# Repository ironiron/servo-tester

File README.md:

Small servo tester designed for Attiny13a. Pulse width 0.5-2.5ms; 3 modes: oscillating, normal and neutrum.

Author: Rafał Mazurkiewicz
contact: raf.mazurkiewicz@op.pl

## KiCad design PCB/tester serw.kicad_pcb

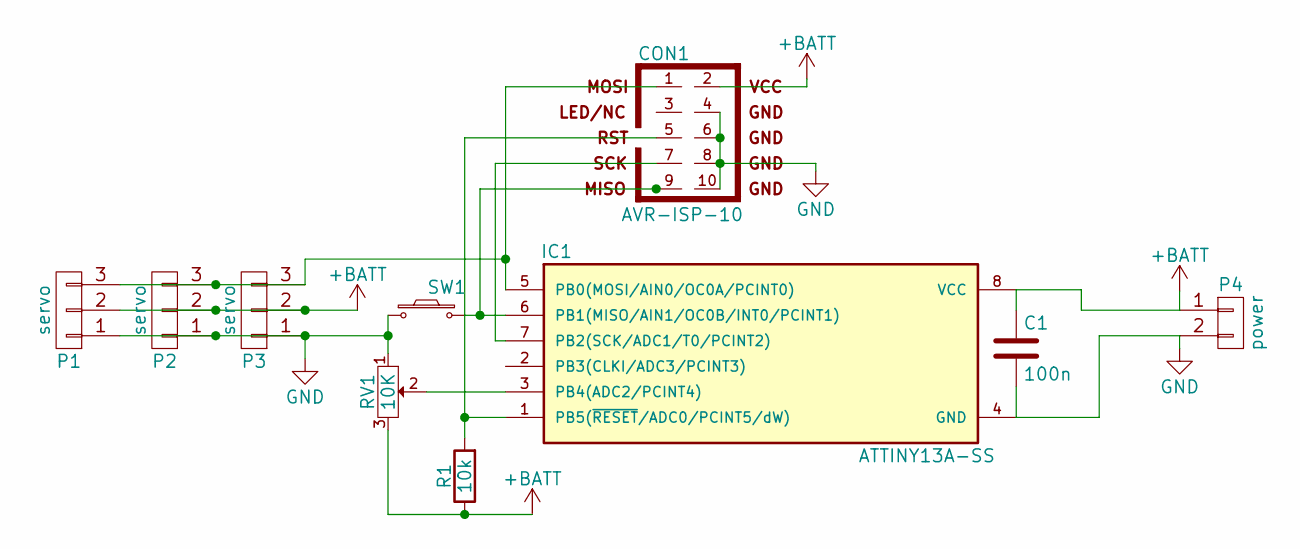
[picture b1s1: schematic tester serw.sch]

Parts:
C1: 100n; C_0805_HandSoldering
CON1: AVR-ISP-10; IDC_Header_Straight_10pins
IC1: ATTINY13A-SS; SOIJ-8_5.3x5.3mm_Pitch1.27mm
P1, P2, P3: servo; Pin_Header_Straight_1x03_Pitch2.54mm
P4: power; Pin_Header_Straight_1x02_Pitch2.54mm
R1: 10k; R_0805_HandSoldering
RV1: 10K; Potentiometer_Alps-RK16-single
SW1: button; SW_SPST_REED_CT05-XXXX-G1

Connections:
+BATT: C1.1, CON1.2, IC1.8 (VCC), P1.2, P2.2, P3.2, P4.1, R1.1, RV1.3
GND: C1.2, CON1.4, CON1.6, CON1.8, CON1.10, IC1.4 (GND), P1.1, P2.1, P3.1, P4.2, RV1.1, SW1.1
unnamed: CON1.1, IC1.5 (PB0(MOSI/AIN0/OC0A/PCINT0)), P1.3, P2.3, P3.3
unnamed: CON1.5, IC1.1 (PB5(~RESET~/ADC0/PCINT5/dW)), R1.2
unnamed: CON1.7, IC1.7 (PB2(SCK/ADC1/T0/PCINT2))
unnamed: CON1.9, IC1.6 (PB1(MISO/AIN1/OC0B/INT0/PCINT1)), SW1.2
unnamed: IC1.3 (PB4(ADC2/PCINT4)), RV1.2

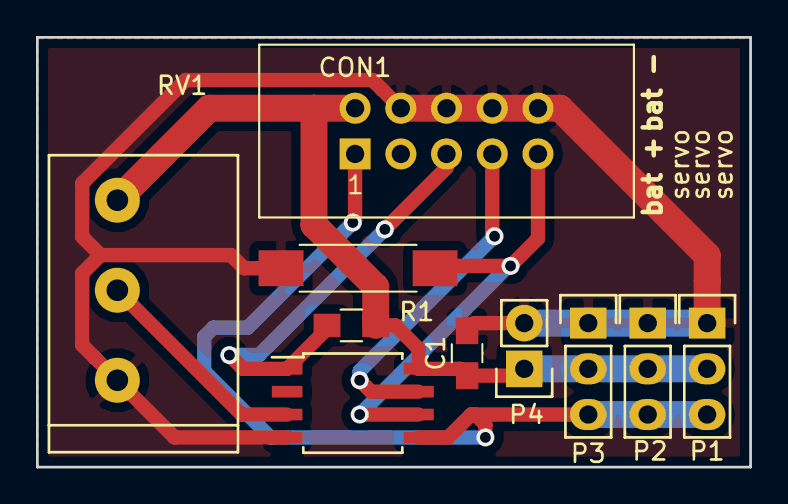
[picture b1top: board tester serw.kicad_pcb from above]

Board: 2 copper layers, 39.6 x 23.9 mm, 10 parts (0 on the bottom side), 7 nets.

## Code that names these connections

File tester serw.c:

/*
 * tester_serw.c
 *
 * Created: 2015-01-10 17:53:29
 *  Author: Rafał Mazurkiewicz
 Servo tester. In period of 20ms sends 0,5-2,5ms impulse to servo.
 potentiometer PB4
 button PB1 INT0 long press (>1s) servo is oscillating, short press- neutrum.
 Return to normal mode by pressing button (if was oscillating), or by moving potentiometer.
 output PB0
 
 tester serw wysyła co ok. 20ms impuls o długości 0,5-2,5ms do serwa.
 Potencjometr na PB4
 Przycisk na PB1 INT0. długie (>1s) naciśnięcie serwo oscyluje, krótkie stoi w neutrum 
 powrót do pracy swobodnej potencjometrem, bądź przyciskiem jeśli wcześniej był w tryb oscylacji.
 wyjście PB0
 */ 

#include <avr/io.h>
#include <util/delay.h>
#include <avr/interrupt.h>

#define button (1<<PB1)
#define output (1<<PB0)
#define potenciometer (1<<PB4)
#define set_output PORTB|=(1<<PB0)
#define clear_output PORTB&=~(1<<PB0)
#define TCNT0_BASE 105 // tick resolution for manipulating PWM lenght is 150, thus 255-150=105.

//SPI related
#define SET_SS //PORTB|=(1<<PB5)
#define SET_CLOCK PORTB|=(1<<PB2)
#define SET_MOSI PORTB|=(1<<PB3)

#define RESET_SS //PORTB&=~(1<<PB5)
#define RESET_CLOCK PORTB&=~(1<<PB2)
#define RESET_MOSI PORTB&=~(1<<PB3)


volatile uint8_t adc=0;
volatile uint8_t remember=0;
volatile uint16_t ticks=0;
volatile uint8_t position=0;
volatile uint8_t overflows_left=0;

enum current_mode {normal, neutral, oscillating} current_mode;
enum direction {left, right} direction;
enum state {waiting, PWM, PWM_overflows} state;
	
void _send_SPI(uint8_t data)
{
	//CPOL=0
	//CPHA=0
	RESET_CLOCK;
	RESET_MOSI;
	RESET_SS;
	for(uint8_t i=0;i<8;i++)
	{
		if((data<<i) & 0x80)
		{
			SET_MOSI;
		}
		else
		{
			RESET_MOSI;
		}
		_delay_us(10);
		SET_CLOCK;
		_delay_us(10);
		RESET_CLOCK;
	}
	SET_SS;
}

void calculate_ticks(void)
{
	switch (current_mode)
	{
		case normal:
		ticks=adc*3/2+75;// 1 adc=10ms; add 75 so begins counting fom 0,5ms.
		
		break;
		
		case neutral:
		ticks=225;//one tick is 6,(6)us, so 225ticks=1,5ms
		overflows_left=0;
		break;
		
		case oscillating:
		adc=adc/20;
		if(direction==left)
		{
			if(position<adc)position=0;// if position-adc<0
			else position=position-adc;
		}
		else
		{
			if(position+adc>200)position=200;
			else position=position+adc;
		}
		if(position==200)direction=left;
		if(position==0)direction=right;
		if(position==0)position=1;
		ticks=position*3/2+75;// 1 adc=10ms
		
		break;
	}
			if(ticks>0xff)
			{
				overflows_left=ticks/0xff;
				ticks=ticks%0xff;
			}
	
}
	
void set_timer_generating(void)
{
	TCCR0B = (1<<CS01); /*up-counting prescaler 8 */
}

void set_timer_waiting(void)
{
	TCCR0B = (1<<CS02); /*up-counting prescaler 256 */
	TCNT0=162; /*interrupt every 19,8 ms (f_cpu= 1200000 Hz)*/
}

ISR(TIM0_OVF_vect)
{
	switch(state)
	{
		case waiting:
			state=PWM;
			set_timer_generating();
			TCNT0=0xff-ticks;	
			set_output;
		break;
		
		case PWM:
			if (overflows_left!=0)
			{
				overflows_left--;
				return;
			}
			clear_output;
			state=waiting;
			set_timer_waiting();
			calculate_ticks();
		break;
	}
}

ISR(INT0_vect)
{
	cli();
	_delay_ms(100);/*debouncing*/
	remember=adc;
	current_mode=neutral;
	ticks=0;
	while(!(PINB & button))
	{
		ticks++;
		_delay_ms(10);
		if(ticks>100) /* long press >1s */
		{
			current_mode=oscillating;
			ticks=0;
		}
	}
	sei();
}

ISR(WDT_vect)
{
	uint16_t temp=overflows_left*0xff+ticks;
	_send_SPI(ADCH);
	_send_SPI(ADCL);
	_send_SPI(temp>>8);
	_send_SPI(temp & 0xff);
}

int main(void)
{
    	DDRB |= output;
	PORTB |=button;

	DDRB |= (1<<PB2)|(1<<PB3);//MOSI SCK
	
	GIMSK |=(1<<INT0); /*interrupt on low level*/
	
	set_timer_waiting();
	state=waiting;
	
	TIMSK0 |= (1<<TOIE0);
	
	ADCSRA |=(1<<ADEN) | (1<<ADPS2);		 /*prescaler 16 */
	ADMUX |=(1<<MUX1); /*input- PB4*/
	
	WDTCR |=  (1<<WDCE) | (1<<WDE); /*Enable watchdog in interrupt mode.
	Setting WDCE and clearing WDE (below) is required in order to disable RESET mode. */
	WDTCR = (1<<WDTIF) | (1<<WDTIE) | (1<<WDP2) | (1<<WDP0);//interrupt every 0,5s

	sei();
	
    while(1)
    {
		ADCSRA |=(1<<ADSC);
		while(ADCSRA & (1<<ADSC))
		adc=ADC/5;	/*result- over 200*/
		if(adc>200)
		{
			adc=200;
		}
		if(remember+30<adc || remember>adc+30)
		{
			if(current_mode==neutral)
			{
				current_mode=normal;
			}
		}
    }
}

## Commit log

2019-01-10 comments and timing update
2019-06-15 added watchdog ISR and software spi...testing
2019-06-16 working
2019-06-16 fix project
